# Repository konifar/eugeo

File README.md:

# eugeo

6 キー × 4 行 × 2 ブロック（48 キー）のスルーホール・オーソリニア 40% キーボード PCB です。
[Lumberjack](https://github.com/peej/lumberjack-keyboard)（Paul James 作、MIT License）をベースに、行を 1 段減らし、Kailh の MX 用ホットスワップソケットに対応させました。

| 真上 | 背面 | 側面（6°） |
|---|---|---|
|  |  |  |

組み上がりの画像のスイッチとキーキャップは、大きさと位置の目安として置いた簡易形状です（`scripts/preview_models.py`）。

## Lumberjack からの変更点

| | Lumberjack Rev 1.8 | eugeo Rev 1.0 |
|---|---|---|
| 配列 | 5 × 12（60 キー） | 4 × 12（6 × 4 × 2、48 キー） |
| スイッチ | はんだ付け | Kailh MX ホットスワップソケット（裏面） |
| マトリクス | 6 行 × 10 列 | 8 行 × 6 列（後述） |
| USB-C | 左上・裏面 | 中央上・裏面（ソケットとの干渉回避） |
| 外形 | 60% トレイマウントケース互換 | 284.9 × 75.35 mm。プレートと基板を M2 穴 8 箇所でサンドイッチし、プレートのタブでガスケットマウント |
| ドーターボード用コネクタ (J3-J5) | あり | 削除 |
| 中央カバー | 2 mm アクリル、M2 10 mm スペーサー 4 本 | 同じ構成（ネジはカバーの四隅） |
| マイコン | ATmega328P-PU（DIP）+ V-USB（USB 1.1 Low Speed） | RP2040 + 2 MB QSPI フラッシュ（USB Full Speed、UF2 書き込み） |
| 電源 | USB 5 V 直結 | MCP1700 で 3.3 V（TO-92） |
| 書き込み | ISP ヘッダ（2x3） | BOOT ボタン + USB（UF2）。ISP ヘッダは不要になったので削除 |

マイコンまわりの表面実装部品（RP2040、フラッシュ、0402 のコンデンサなど）は JLCPCB に実装してもらい、それ以外はスルーホール部品のまま残しています。
上部の左右に 1 個ずつの LED、水晶（HC49）、セラミック・電解コンデンサ、LDO（TO-92）、アキシャル抵抗、タクトスイッチ、ダイオード列が中央に並ぶ、Lumberjack の「部品を見せる」見た目を踏襲しています。

## マトリクス

左右のブロックで行を分け、列を共有させた 8 行 × 6 列です。
左右の対称位置の列（左 C0 と右 C11 など）を基板下端の 1 本の配線で共有するので、ROW の配線が MCU をまたがずに済みます。
RP2040 の左辺のピンから左ブロックの行・列 3 本・LED1、右辺のピンから右ブロックの行・列 3 本・LED2 を出し、下辺は水晶と RUN、上辺は QSPI フラッシュと USB に使っています。

| 物理位置 | マトリクス |
|---|---|
| 左ブロック (row r, col c) | ROW r, COL c |
| 右ブロック (row r, col 6+j) | ROW r+4, COL 5-j |

| 設定 | 値 |
|---|---|
| MATRIX_ROW_PINS | GP3, GP4, GP5, GP6, GP26, GP25, GP24, GP23 |
| MATRIX_COL_PINS | GP9, GP10, GP11, GP20, GP19, GP18 |
| DIODE_DIRECTION | COL2ROW |
| LED1 (赤) / LED2 (緑) | GP1 / GP28（上部の左右） |
| BOOT ボタン | QSPI_SS（RP2040 標準の BOOTSEL。1k 経由で GND に落とす） |

## ファイル構成

| パス | 内容 |
|---|---|
| `eugeo.kicad_pro` / `.kicad_sch` / `.kicad_pcb` | KiCad 9 プロジェクト |
| `symbols/`, `footprints/eugeo.pretty/` | プロジェクト専用シンボル・フットプリント（ホットスワップソケット、USB-C、M2 穴） |
| `plates/` | スイッチプレート（ガスケット用タブ付き、左右共通で 2 枚注文）、中央カバー、ボトムプレートの KiCad データと DXF |
| `case/` | Mojo60 風の丸いガスケットマウントケース（下トレイ `eugeo-case-bottom` + 上フレーム `eugeo-case-top`）と中央カバーの STEP / STL |
| `foam/` | プレートフォーム・ケースフォーム・ガスケットパッドの DXF と原寸 PDF |
| `lasercut/yushakobo/` | 遊舎工房レーザー加工サービス用の SVG（中央カバー / スイッチプレート / フォーム） |
| `jlcpcb/` | JLCPCB 実装用 BOM / CPL（表面実装部品とホットスワップソケット） |
| `jlcpcb/full/` | USB-C とスルーホール部品まで JLCPCB に実装してもらう場合の BOM / CPL |
| `gerbers/*.zip` | 製造用ガーバー（PCB、プレート、ボトム） |
| `firmware/qmk/keyboards/eugeo/` | QMK 用キーボード定義とキーマップ（default / via） |
| `firmware/*.uf2` | ビルド済みファームウェア |
| `scripts/` | 回路図・基板・裏面アート（`stump_art.py`）を生成するスクリプト一式 |

## 生成手順

回路図と基板は `scripts/design.py` を唯一の定義として生成しています。
部品配置やネットを変えるときは `design.py` を編集して再生成してください。

```bash
FREEROUTING_JAR=/path/to/freerouting-2.1.0.jar scripts/build_all.sh
```

1. `gen_schematic.py` で回路図を生成し、`check_netlist.py` で `design.py` とネットを照合
2. `build_pcb.py` で部品配置と、キー部分・ダイオード列・USB 端子・RP2040 まわりの配線を引く。RP2040 は電源ピンをパッドの内側の +3V3 リングでまとめ、QSPI・水晶・パスコン・各ピンの引き出しまでを手配線している
3. `route.sh` で残り（引き出した先から各部品まで）を Freerouting 2.1.0 で自動配線
4. `cleanup_dangling.py` で余った配線を削除し、`fill_zones.py` で表裏の GND ベタを流し、`stump_art.py` で裏面のアートを描く
5. DRC（回路図との整合チェック込み）

Freerouting の結果は実行ごとに変わり、まれに未配線が残ります。その場合は `build_all.sh` を再実行してください。
Freerouting 2.1.0 は Java 21 で動きます（2.2 以降は Java 25 が必要）。
初回起動時にできる設定ファイル（macOS では `$TMPDIR/freerouting/freerouting.json`）はテレメトリが有効なので、`allow_telemetry` を `false` にしておくことを勧めます。

製造データは次のコマンドで出力します。

```bash
scripts/export_fab.sh
```

## 製造（JLCPCB）

2026-10-06 に JLCPCB / JLC3DP の見積もりページへアップロードし、次のとおり受け付けられることを確認しました（カート投入・注文はしていません）。

| 部品 | ファイル | JLCPCB の認識 | 見積もり（参考） |
|---|---|---|---|
| PCB | `gerbers/eugeo.zip` | 2 層、284.9 × 75.35 mm | 5 枚 ¥2,269 + 送料 ¥1,536 |
| スイッチプレート | `gerbers/eugeo-plate.zip` | 2 層、113.45 × 75.35 mm。外形レイヤーにスイッチ穴 24 個と M2 穴 4 個（ガスケット用タブを付ける前の版。今の版はタブ込みで 118.45 × 85.35 mm） | 5 枚 ¥630 |
| ケース | `case/eugeo-case.step` | 302.9 × 93.4 × 29.9 mm、198.09 cm³（ふちを上げる前・一体型の版） | 9600 Resin 白 1 個 ¥2,978 + 送料 ¥1,139。MJF ナイロン（PA12）なら グレー ¥11,651、黒染め ¥12,945（2026-10-17） |

PCB の注文設定は既定値（FR-4、1.6 mm、HASL）のままで問題ありません。色は好みで変えてください。
スイッチプレートは銅箔のない基板として注文します。JLCPCB の 2D プレビューでは穴が描かれませんが、Gerber Viewer の Layers 表示で外形に穴が入っていることを確認できます。左右共通なので 2 枚以上あれば足ります。
ボトムプレート（`gerbers/eugeo-bottom.zip`）はケースを使わない場合だけ必要です。

ケースは JLC3DP の 3D Printing で `case/eugeo-case-bottom.step` と `case/eugeo-case-top.step`（または `.stl`）の 2 つをアップロードし、素材に MJF ナイロン（PA12）を選びます。
MJF の最大造形サイズ（380 × 284 × 380 mm）に収まります。
すき間は MJF の寸法公差（±0.3 mm、100 mm を超える部分は ±0.3 %、長さ 303 mm で片側約 0.45 mm）と、内外を塗装したときの塗膜（1 面 0.1〜0.2 mm）を見込んで決めています（ネジ穴 φ2.8、ネジ頭の座ぐり φ5.0、ナット穴 二面幅 4.7 mm）。SLA レジンでも同じデータで作れます。
2026-11-14 は SLA の 9600 Resin 白（Sanding-General Sanding）で注文し、塗装は自分でする（上下で ¥3,265、製作 3 日。MJF PA12 は無塗装で ¥11,905、黒マット塗装付きで ¥13,867）。自分で塗るときは、ネジ穴とナット穴をマスキングしてから黒のサーフェイサー → つや消し黒 → UV カットのつや消しクリアの順に吹く。

### 表面実装部品とソケットの実装を JLCPCB に頼む

RP2040 まわりの表面実装部品（表面）とホットスワップソケット 48 個（裏面）を JLCPCB の PCBA で実装し、残りのスルーホール部品は自分ではんだ付けする想定です。
表裏両面の実装になるので Standard PCBA を選び、Assembly Side は **Both Sides** にして次のファイルをアップロードします。

| ファイル | 内容 |
|---|---|
| `jlcpcb/eugeo-bom.csv` | ソケット（LCSC C41430893）と表面実装部品（RP2040 C2040、W25Q16JVSSIQ C131025、USBLC6-2SC6 C7519、0402 のコンデンサ・抵抗。R7 / R8 / C12 / C13 / U4 は裏面） |
| `jlcpcb/eugeo-cpl.csv` | 実装座標（ガーバーと同じ原点）。ソケットは本体中心・裏面・回転 0、表面実装部品は KiCad の部品位置 |

2026-10-08 に実際にアップロードして確認した結果です（カート投入・注文はしていません）。

- ガーバー: 2 層、284.9 × 75.35 mm として受け付け。Standard PCBA では JLCPCB が上下に 5 mm の捨て基板（エッジレール）を付けるので、届いた基板はレールを折って外す（有料の Depanel オプションで外してもらうこともできる）
- BOM: 7 品目すべてが LCSC 部品に一致（RP2040 C2040、W25Q16JVSSIQ C131025、USBLC6-2SC6 C7519、0402 のコンデンサ・抵抗、ソケット C41430893）
- 部品配置プレビューで、RP2040・フラッシュ・USBLC6 の 1 番ピンとリードがフットプリントに合うことを確認。KiCad の角度のままではフラッシュ（SOIC-8、表）と USBLC6（SOT-23-6、裏）が 90° ずれていたので、`scripts/export_jlc_pcba.py` の `ROT_OFFSET` で補正済み。USBLC6 は 180° 間違えると GND と VBUS が入れ替わるので、部品を変えたときは必ずプレビューで確かめる
- ソケットの回転は 2026-10-06 に確認済み（突起が φ3.05 穴に、端子がパッドに重なる）
- 見積もり: 5 枚で ¥18,706（PCB ¥2,490、PCBA ¥16,215。うち初期費用 ¥8,117、ステンシル ¥2,607、部品 ¥3,406）、送料別

Kailh 純正ソケット（C5184526）にしたい場合は `scripts/export_jlc_pcba.py` の `LCSC` を書き換えてください。

### すべての部品の実装を JLCPCB に頼む

USB-C とスルーホール部品（ダイオード 48 本、抵抗、コンデンサ、水晶、レギュレータ、タクトスイッチ、LED）まで JLCPCB に付けてもらう場合は、`jlcpcb/` の代わりに `jlcpcb/full/` をアップロードします（`python3 scripts/export_jlc_pcba.py --full` で生成）。はんだ付けは不要になり、届いたらスイッチを挿すだけです。

2026-10-08 にアップロードして確認した結果です（カート投入・注文はしていません）。

- BOM: 22 品目すべてが LCSC 部品に一致し、在庫あり
- スルーホール部品の座標は KiCad の原点（1 番ピン）ではなくパッドの中心にしている。USB-C は SMD なので部品位置のまま
- 部品配置プレビューで向きを確認。JLCPCB のモデルでは 3 mm LED のカソードと USB-C の差し込み口が逆向きだったので、`ROT_OFFSET` で 180° 補正済み
- 見積もり: 5 枚で ¥27,679（PCB ¥2,490、PCBA ¥25,188。うち初期費用 ¥8,117、ステンシル ¥2,607、部品 ¥6,949、フィーダー ¥1,954、手はんだ ¥569、手作業実装 ¥1,989、治具 ¥2,607）、送料別。表面実装部品とソケットだけの場合より ¥8,973 高い
- コンデンサ C6 / C7（C1620326）は単価が高く在庫も少なめ（確認時 34 個）、レギュレータ U3（C511277）も在庫 349 個。注文時に在庫切れなら同等品に差し替える

## 裏面のデザイン

基板の裏面は「凍てついた切り株」がテーマです（`scripts/stump_art.py`、`build_all.sh` の中で自動生成）。

- 裏返して左側（表から見て右ブロックの 1 段目と 2 段目の間）に、ケース背面の刻印と同じ Futura の「EUGEO」ロゴを大きく入れている。文字の高さ 7.5 mm、両側に細い線と丸を添える。文字の輪郭は `scripts/logo_outline.py` で `scripts/logo_eugeo.json` に書き出したもの

- 中央に年輪・樹皮・干割れのある切り株をシルクで描き、左右の端に向かって霜の結晶（シダ状の霜）が伸びる
- キーの並ぶ部分にはシルクの雪の結晶を散らす
- 大きめの雪の結晶 7 個はソルダーレジストの開口で、GND ベタの銅がそのまま（HASL なら銀色に）見える。配線・ビア・穴のない GND ベタの上にだけ置く
- シルクはパッド・穴・既存の文字の周りで自動的に切り取り、DRC の警告が出ないようにしている

レジストの色は青（Blue）を勧めます。白いシルクと銀色の結晶が氷のように見えます。

## ケース

Mojo60 を意識した、角と上下のふちを大きく丸めたガスケットマウントのケースです。プレートの中ほどの高さで、下トレイと上フレームの 2 つに分かれています。

| 項目 | 値 |
|---|---|
| 外形 | 302.9 × 93.4 mm、高さ 手前 23.1 mm / 奥 32.9 mm |
| 傾斜 | 6° |
| 角の丸み | 平面 R12、上面のふち R6.5、底面のふち R4.5 |
| ふち | プレート上面から 6.5 mm 上（スイッチの上部が隠れ、キーキャップはその上に出る高さ） |
| 基板と壁のすき間 | 1.0 mm（キーキャップと壁の間は約 1.1 mm） |
| 底面 | 肉抜きして、幅 7 mm のふちで接地。肉抜きには厚さ 2 mm の格子リブ（前後 7 本、左右 1 本）を入れ、床の鳴りと反りを抑える。ネジ穴のまわりは肉を 1.5 mm 以上残す |
| 分割 | プレートの厚さの中央（基板上面から 4.25 mm）で上下に分割。下トレイ 25.2 mm、上フレーム 7.3 mm |
| 刻印 | 奥の壁に「EUGEO」の銘板（後述） |

### 刻印

奥の壁の USB-C の横（背面から見て右）に、銘板風の刻印を入れています。
USB-C の切り欠きと同じ高さ 8.5 mm の長円を 0.6 mm 掘り下げ、Futura の「EUGEO」（文字高さ約 4.4 mm、字間広め）と両端の小さな鋲を元の壁面の高さで残しています。
USB-C の切り欠きと形・高さを揃えて、背面の 2 つの要素が並んで見えるようにしました。

文字・フォント・位置・深さは `scripts/case.py` の `BADGE_*` 定数で変えられます。

寸法は `scripts/case.py` の先頭にある定数で変えられます。再生成の手順は次のとおりです。

```bash
uv venv --python 3.12 .venv && uv pip install --python .venv/bin/python build123d
.venv/bin/python scripts/case.py
kicad-cli pcb export step --subst-models -o /tmp/eugeo-pcb.step eugeo.kicad_pcb
.venv/bin/python scripts/check_case_fit.py /tmp/eugeo-pcb.step   # 基板・部品・プレートとの干渉チェック
```

### ガスケットマウント

左右のスイッチプレートの外周にタブ（幅 10 mm、外へ 5 mm）が 5 本ずつあり、ケースの壁の溝の中で上下から PORON のパッドに挟まれています。
基板はスペーサーでプレートにぶら下がっていて、ケースのどこにも触れません。打鍵の力はパッドで受けるので、たわみと音がやわらかくなります。

| 項目 | 値 |
|---|---|
| タブ | 1 枚のプレートに奥 2 本・手前 2 本・外側 1 本（左右で計 10 本）。左右共通の形で、右側は裏返して使う |
| パッド | 3 mm PORON を 10 × 4 mm に切ったもの 20 個（タブの上下に 1 個ずつ）。溝の中では 2.2 mm に縮む（約 27%） |
| 溝 | タブより左右に 0.5 mm、先端に 1 mm 大きい。高さはプレート 1.5 mm + パッド 2.2 mm × 2 |
| 基板のすき間 | 壁とは 1 mm。ケースの底とは、キー部分が 2.8 mm（3 mm のケースフォームを 0.2 mm つぶして基板の裏に当てる）、中央の部品エリアが 5 mm |
| 上下の固定 | M2×10 なべネジ 8 本を底から通し、上フレームに埋めた M2 ナットで締める |

`scripts/check_case_fit.py` で、基板・部品・プレート・タブがケースに当たらないことと、10 本のタブすべてで上下のパッドの厚みが確保されていることを確かめています。

### 組み立て

インサートを使わずに済むよう、上下のケースは底からネジで留めます。

1. 基板の上面の M2 穴 8 か所（H1〜H8）に M2 3.5 mm のメス-メススペーサーを立て、基板の裏から M2×3 で留める
2. スイッチをプレートにはめ、基板のソケットに差し込み、プレートの上から M2×3 でスペーサーに留める（右のプレートは左と同じものを裏返して使う）
3. 中央カバーを付ける（後述）
4. 上フレームのナット穴（下面）に M2 ナットを 8 個入れる。抜けやすい場合はマスキングテープか少量の接着剤で仮止めする
5. 下トレイの溝の底と、上フレームの溝の天井にガスケットパッドを貼る（PORON は粘着なしなので、両面テープで軽く留める）
6. ケースフォームを下トレイの一段高い床に置き（左右で形が違うので `L` / `R` を確かめ、裏返さない）、基板とプレートの組を載せてタブを溝に合わせる
7. 上フレームをかぶせ、底から M2×10 を 8 本締める。締めすぎるとパッドがつぶれてガスケットの効果がなくなるので、上下が接したところで止める

奥の壁の USB-C 用の切り欠きは 14 × 9.5 mm です（基板がパッドの上で動くぶん、一体型のときより 1 mm 高くしています）。プラグのモールド部分がこれより大きいケーブルは奥まで刺さりません。
底面の四隅に平らな面を残してあるので、直径 8〜10 mm のゴム足を 4 個貼ってください（中心はケースの左右の端から約 10 mm、前後の端から約 10 mm）。

## 中央カバー

Lumberjack と同じく、中央の部品（ダイオード列・MCU・USB 周り）を透明な板で覆えます。

| 項目 | 値 |
|---|---|
| 大きさ | 56.2 × 75.35 mm、角 R3、厚さ 2 mm |
| 取り付け | カバーの四隅に合わせた基板の M2 穴 4 か所（H9〜H12）に M2 10 mm のメス-メススペーサーを立て、下から M2×4 で基板に、上から M2×4 でカバーを留める |
| 高さ | カバーの下面は基板上面から 10 mm。下でいちばん高い LED1（8.29 mm）との間に 1.71 mm のすき間 |
| ケースとの関係 | カバーの上面はケースのふちより約 0.5 mm 上。ケース・キーキャップとは重ならない |

| ファイル | 用途 |
|---|---|
| `plates/eugeo-cover.dxf` | アクリル板のレーザーカット用（推奨） |
| `case/eugeo-cover.step` / `.stl` | 3D プリントや CNC 用 |
| `gerbers/eugeo-cover.zip` | JLCPCB で FR4 板として作る場合（不透明になる） |

JLCPCB の基板サービスでは透明な板は作れないため、透明にしたい場合はアクリルのレーザーカットサービスに DXF を出してください。
JLC3DP の SLA で作る場合は、見積もり画面で透明系のレジンが選べるか確認してください。

## フォーム

打鍵音とたわみの調整用の 2 種類のフォームと、ガスケットマウント用のパッドの型を用意しました。プレートフォームは左右同じ形なので 1 つの型で 2 枚切り、片方は裏返して使います。ケースフォームはソケットの向きが左右で同じため、左用と右用で形が違います（裏返さずにそのまま置く）。

| ファイル | 位置 | 推奨素材 | 形 |
|---|---|---|---|
| `foam/eugeo-plate-foam` | プレートと PCB の間（3.5 mm） | 3 mm PORON | プレートと同じ外形、スイッチ下部を逃がす 14.5 mm 角穴、スペーサー用 φ4.4 穴 |
| `foam/eugeo-case-foam-left` / `-right` | PCB とケース底の間（キー部分 2.8 mm） | 3 mm PORON | キー部分のみ（中央の部品エリアは空ける）。ホットスワップソケット・はんだ付けの足・スイッチの中心軸と足を 0.5 mm 大きく逃がす穴と、基板の裏のネジ頭を逃がす φ7 穴。外形との間が 2 mm 未満になるところは切り欠きにしている |
| `foam/eugeo-gasket-pad` | プレートのタブの上下（ケースの溝） | 3 mm PORON | 10 × 4 mm、20 個 |

`.dxf` はレーザーカット業者向け、`-1to1.pdf` は手で切るための原寸の型紙です。PDF は A4 横で、倍率 100% で印刷し、100 mm のスケールバーで寸法を確かめてから使ってください。
ケースのキー部分の床は基板の裏から 2.8 mm の高さに上げてあり、3 mm のケースフォームがソケットを避けながら基板の裏に軽く当たります。ソケットやスイッチの足にフォームが当たらないことは `scripts/check_case_fit.py` で確かめています。
JLCPCB ではフォームのカットは扱っていないため、遊舎工房のレーザー加工（下記）に出すか手で切ってください。
スイッチプレートは、ケースの内側に 1 mm のすき間で収まり、ケースのふちより 6.5 mm 低い位置に来ることを確認済みです。

## 遊舎工房のレーザー加工

[遊舎工房のレーザー加工サービス](https://yushakobo.jp/lasercut/)に、そのまま入稿できる SVG を `lasercut/yushakobo/` に用意しました。
遊舎工房配布の Inkscape テンプレートを土台にし、注文サイズの作業領域だけを残しています。

| ファイル | 注文するサービス / 素材 / 厚さ / サイズ | 中身 |
|---|---|---|
| `eugeo-cover_acrylic-clear-2mm_450x300.svg` | [レーザー加工サービス](https://shop.yushakobo.jp/products/lasercut)（アクリル）/ アクリル クリア / 2mm / 450x300 | 中央カバー 26 枚（縦向き 7 枚 × 3 段 + 横向き 5 枚） |
| `eugeo-switch-plate_pom-1.5mm_490x245.svg` | [レーザー加工サービス（その2）](https://shop.yushakobo.jp/products/lasercut-2) / POM / 1.5mm / 490x245 | ガスケット用タブ付きスイッチプレート 8 枚（4 台分。左右共通、右は裏返して使う）。隣り合うプレートのタブを互い違いにかみ合わせ、4 mm 空けて並べている |
| `eugeo-foam_poron-3mm_500x300.svg` | レーザー加工サービス（その2）/ フォーム / 3mm / 500x300 | キーボード 3 台分。プレートフォーム 6 枚 + ケースフォーム左右 3 組 + ガスケットパッド 60 個（1 段目〜3 段目が 1 台分ずつ） |

- 穴などの内側はカット①（赤）、外形はカット②（青）です。内側を先に切ってから部品を切り離す順番になります
- 線幅 0.001 mm、塗りなし、RGB、ファイル名は半角英数字です。シート端から 3.5 mm 以上、部品同士は 3 mm 以上空けています（規定は 3 mm / 2 mm 以上。部品同士はタブ込みの外形どうしの距離で `check_lasercut_svg.py` が確かめる）
- レーザーは線の上を切るため、穴は線より少し大きく、外形は少し小さく仕上がります。POM プレートのスイッチ穴（14.0 mm）が緩い場合は、注文時に相談してください
- スイッチプレートは JLCPCB の FR4（`gerbers/eugeo-plate.zip`、1.6 mm）と POM のどちらで作っても同じ形です。ガスケットマウントでは、たわむ POM のほうが向いています

テンプレートはリポジトリに含めていません。作り直すときは、遊舎工房の [Laser_Cut_template](https://drive.google.com/drive/folders/1BYeC-_gsrWUxI49BNqbQBk6OOC30LgTS) の Inkscape フォルダにある `Laser_acrylic_template.svg`、`Laser_POM_template.svg`、`Laser_Poron_template.svg` を 1 つのフォルダに置き（POM / Poron はファイル名を小文字の `pom` / `poron` にする）、次を実行します。

```bash
python3 scripts/export_yushakobo_svg.py <テンプレートのフォルダ>
python3 scripts/check_lasercut_svg.py
```

## 組み立て（基板）

- ホットスワップソケットと USB-C は裏面、それ以外の部品は表面に付けます
- ダイオードは帯（カソード）を MCU 側に向けます。左列はシルクの右側、右列は左側がカソードです
- プレートと PCB の間は 3.5 mm（1.5 mm 厚プレートでスイッチ底面が PCB に接する高さ）です
- ケースを使わずボトムプレートで挟む場合は、裏面の USB-C とソケットを避けるため PCB とボトムの間を 8 mm 程度空けます

## ファームウェア

`firmware/qmk/keyboards/eugeo` を qmk_firmware の `keyboards/` にコピーしてビルドします。
2026-10-07 時点の qmk_firmware でビルドできることを確認済みです。ビルド済みの `firmware/eugeo_default.uf2` / `firmware/eugeo_via.uf2` も置いてあります。

```bash
qmk compile -kb eugeo -km via
```

RP2040 は ROM にブートローダーを持っているので、ブートローダーの書き込みは要りません。

1. BOOT を押したまま RESET を押して離す（何も書き込まれていない新品の RP2040 は USB をつなぐだけでよい）
2. `RPI-RP2` という USB ドライブとして認識される
3. `eugeo_via.uf2` をそのドライブにコピーすると、書き込み後に自動で再起動する

`qmk flash -kb eugeo -km via` でも同じことができます。キーマップに `QK_BOOT` を割り当てておけば、BOOT ボタンを使わずに書き込みモードに入れます。

### Remap / VIA

`via` キーマップは VIA 対応（`VIA_ENABLE = yes`）で、[Remap](https://remap-keys.app) と VIA のどちらからでもキー配置を変えられます。

1. Chrome か Edge で Remap を開き、「Configure」から eugeo を接続する
2. Remap のカタログに未登録のうちは定義ファイルを求められるので、`firmware/via/eugeo.json` を読み込む

`firmware/via/eugeo.json` は VIA v3 形式の定義ファイルで、物理配列どおり左右ブロックの間を 3U 空けています。VIA の Design タブでもそのまま読み込めます。
Remap のカタログに登録すると、Remap の画面からファームウェアの書き込み（UF2 のダウンロードとコピーの案内）もできるようになります。

Remap のカタログに登録すれば、定義ファイルを読み込まなくても自動で認識されます。登録は Remap に GitHub アカウントでログインして申請し、ファームウェアのソースの場所（GitHub のリポジトリなど）を示します。
VID / PID（`0x6B6E` / `0x4547`）は自分で決めた値です。登録前に、他のキーボードと重複していないか Remap 上で確認してください。

## 動作の検証

実機は作っていないため、基板データからの検証で、はんだ付けすれば動くことを確認しています。

- KiCad の DRC: 違反 0、未接続 0、回路図との整合 OK。ERC も 0 件
- `scripts/verify_design.py`（59 項目すべて合格）
  - RP2040 のシンボルのピン名がデータシート（QFN-56）と一致すること
  - 電源: IOVDD 6 本・ADC_AVDD・VREG_VIN・USB_VDD が +3V3、VREG_VOUT が DVDD 2 本に、パスコンの数と RP2040 からの距離、MCP1700 のピン配置
  - 12 MHz 水晶と 1k 直列抵抗、22 pF、RUN のプルアップと RESET、BOOT（QSPI_SS を 1k で GND へ）
  - QSPI フラッシュの 8 ピンが RP2040 の QSPI 信号と一致すること
  - USB: D+ / D- が 27Ω 経由で USB_DP / USB_DM に、USBLC6、CC の 5.1k、VBUS のポリスイッチ
  - LED とコンデンサの極性、ダイオードの向き（COL2ROW）、QMK の LED ピン設定
  - 48 キーすべてについて、基板上の行・列の GPIO が QMK の `keyboard.json` と一致すること
- RP2040 まわりは、電源ピンをパッドの内側の +3V3 リングでまとめ、+1V1 は裏面経由で 3 ピンをつなぎ、QSPI・水晶・パスコン・行と列の引き出しまでを手配線しています。0.4 mm ピッチの間をすり抜ける配線はありません
- 中央カバー: カバー下面と部品の最小すき間 1.71 mm（LED1）、カバーとケース・部品の干渉 0（`scripts/check_case_fit.py`）
- ソケットのフットプリント: パッド位置・サイズが [keyswitch-kicad-library](https://github.com/perigoso/keyswitch-kicad-library) の SW_Hotswap_Kailh_MX_1.00u と一致。ソケットの突起が入る穴は同ライブラリに合わせて φ3.05 mm

```bash
KP=/Applications/KiCad/KiCad.app/Contents/Frameworks/Python.framework/Versions/Current/bin/python3
$KP scripts/verify_design.py
```

### 発注前チェック

発注の前に `scripts/preorder_check.py` を実行してください（2026-10-07 時点で 23 項目すべて合格）。DRC で見えない次の点を確かめます。

- 前の版との差分が、意図した部品の追加・削除だけであること（ほかのパッドの位置と接続が変わっていない）
- 全部品が `design.py` どおりの位置・向き・面にあり、外形も設計どおりであること
- スペーサー・ネジ頭が当たる範囲に、むき出しの銅箔がないこと。ビアがすべてレジストで覆われていること（マスクのガーバーでも確認）
- 実際の基板の最小値（線幅 0.15、ビア φ0.3 / 0.6、穴、スロット、シルク文字 1.0 mm）が JLCPCB の製造基準を満たすこと
- `gerbers/eugeo.zip` が今の基板から出したものと一致し、ドリルデータに M2 穴 12 個が設計位置どおりにあること
- JLCPCB の実装座標（ソケットと表面実装部品）と LCSC 番号、スイッチプレート・中央カバー・ボトムプレートの穴が基板の穴と一致すること
- 遊舎工房向け SVG が入稿ルールを満たすこと、59 項目の機能チェックが通ること

```bash
$KP scripts/preorder_check.py --base <前回発注した版の git リビジョン>
```

## 未検証の点

- 試作していません。上記の検証、ケースとの干渉チェックは通っています
- JLCPCB の部品の回転角はプレビューで確認しただけです。部品を変えたら注文時の配置プレビューで 1 番ピンの向きを確かめてください（上の「表面実装部品とソケットの実装を JLCPCB に頼む」）
- USB-C コネクタ（TYPE-C-31-M-12）は 0.5 mm ピッチの SMD で、手はんだでは一番難しい部品です（Lumberjack と同じ部品）
- ケースの USB-C 部はコネクタの 3D モデルがないため、寸法計算だけで確認しています
- ホットスワップソケットのフットプリントは keyswitch-kicad-library と同寸で、JLCPCB の部品配置とも一致しましたが、実物のソケットでの勘合は未確認です

## License

ハードウェア（回路図・基板・プレート・ケース・フォーム）とスクリプトは MIT License です。Lumberjack の著作権表示を `LICENSE` に残しています。
`firmware/qmk/` 以下のファームウェアは QMK に合わせて GPL-2.0-or-later です。

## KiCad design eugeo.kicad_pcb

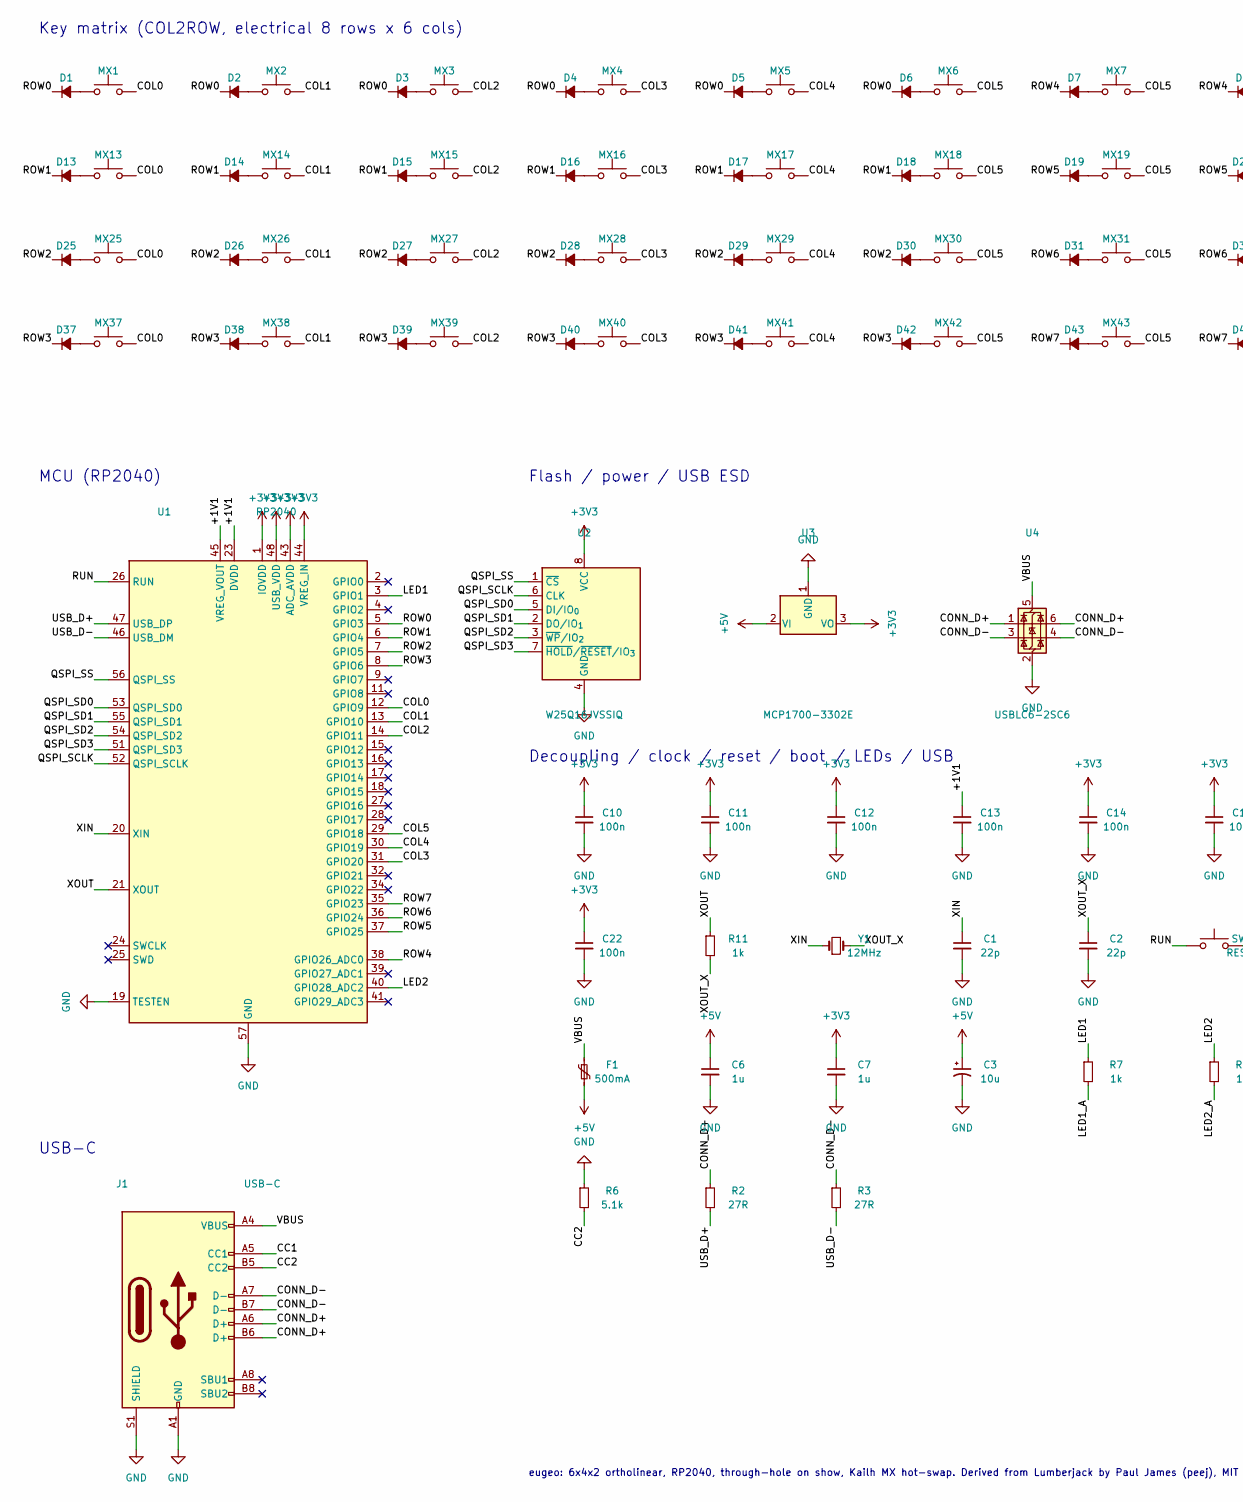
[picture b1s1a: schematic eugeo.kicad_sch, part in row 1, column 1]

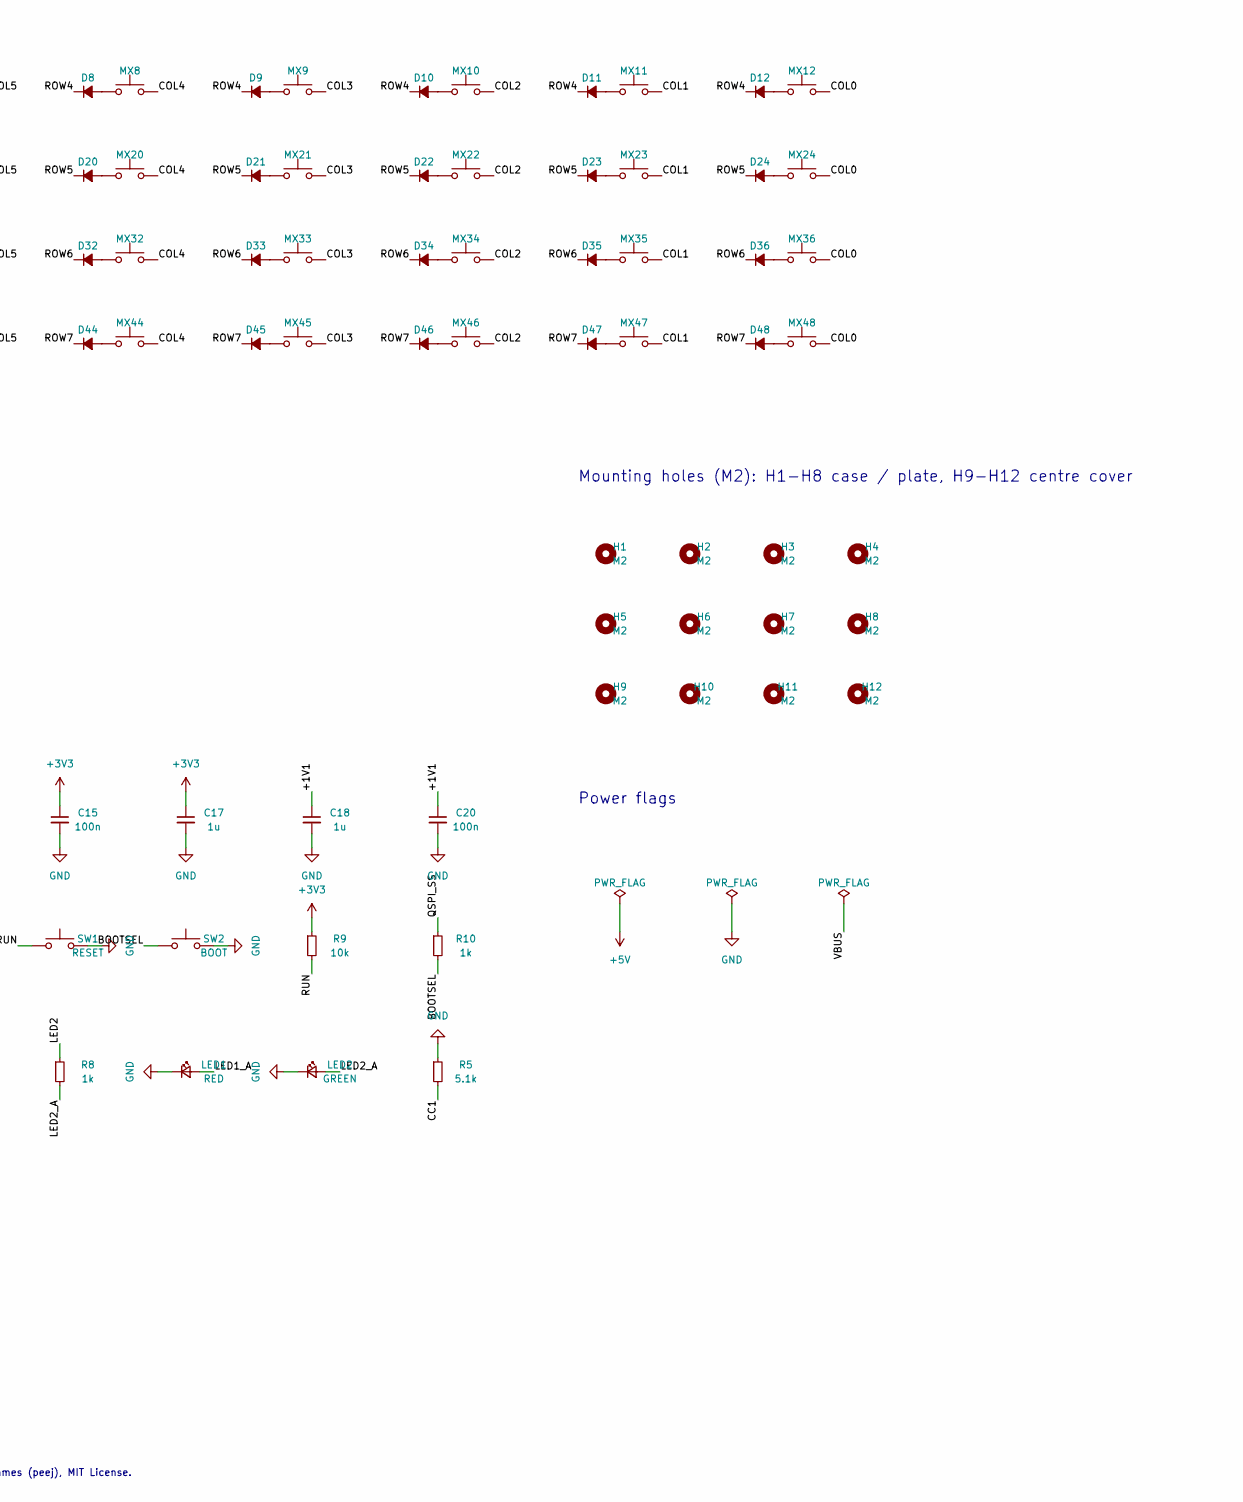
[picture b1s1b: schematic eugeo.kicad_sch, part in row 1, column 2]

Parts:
C1, C2: 22p; C_Disc_D3.0mm_W1.6mm_P2.50mm
C3: 10u; CP_Radial_D4.0mm_P1.50mm
C6, C7: 1u; C_Disc_D3.0mm_W2.0mm_P2.50mm
C10, C11, C12, C13, C14, C15, C20, C22: 100n; C_0402_1005Metric
C17, C18: 1u; C_0402_1005Metric
D1, D2, D3, D4, D5, D6, D7, D8, D9, D10, D11, D12, D13, D14, D15, D16, D17, D18, D19, D20, D21, D22, D23, D24, D25, D26, D27, D28, D29, D30, D31, D32, D33, D34, D35, D36, D37, D38, D39, D40, D41, D42, D43, D44, D45, D46, D47, D48: 1N4148; D_DO-35_SOD27_P7.62mm_Horizontal
F1: 500mA; Fuse_1206_3216Metric
H1, H2, H3, H4, H5, H6, H7, H8, H9, H10, H11, H12: M2; MountingHole_M2_NPTH
J1: USB-C; TYPE-C-31-M-12
LED1: RED; LED_D3.0mm
LED2: GREEN; LED_D3.0mm
MX1, MX2, MX3, MX4, MX5, MX6, MX7, MX8, MX9, MX10, MX11, MX12, MX13, MX14, MX15, MX16, MX17, MX18, MX19, MX20, MX21, MX22, MX23, MX24, MX25, MX26, MX27, MX28, MX29, MX30, MX31, MX32, MX33, MX34, MX35, MX36, MX37, MX38, MX39, MX40, MX41, MX42, MX43, MX44, MX45, MX46, MX47, MX48: MX; MX_Hotswap_Kailh
R2, R3: 27R; R_Axial_DIN0204_L3.6mm_D1.6mm_P7.62mm_Horizontal
R5, R6: 5.1k; R_Axial_DIN0204_L3.6mm_D1.6mm_P7.62mm_Horizontal
R7, R8, R11: 1k; R_0402_1005Metric
R9: 10k; R_Axial_DIN0204_L3.6mm_D1.6mm_P7.62mm_Horizontal
R10: 1k; R_Axial_DIN0204_L3.6mm_D1.6mm_P7.62mm_Horizontal
SW1: RESET; SW_PUSH_6mm
SW2: BOOT; SW_PUSH_6mm
U1: RP2040; QFN-56-1EP_7x7mm_P0.4mm_EP3.2x3.2mm
U2: W25Q16JVSSIQ; SOIC-8_5.3x5.3mm_P1.27mm
U3: MCP1700-3302E; TO-92_Inline_Wide
U4: USBLC6-2SC6; SOT-23-6
Y1: 12MHz; Crystal_HC49-4H_Vertical

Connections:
+3V3: C7.1, C10.1, C11.1, C12.1, C14.1, C15.1, C17.1, C22.1, R9.1, U1.1 (IOVDD), U1.10 (IOVDD), U1.22 (IOVDD), U1.33 (IOVDD), U1.42 (IOVDD), U1.43 (ADC_AVDD), U1.44 (VREG_IN), U1.48 (USB_VDD), U1.49 (IOVDD), U2.8 (VCC), U3.3 (VO)
+5V: C3.1, C6.1, F1.2, U3.2 (VI)
/+1V1: C13.1, C18.1, C20.1, U1.23 (DVDD), U1.45 (VREG_VOUT), U1.50 (DVDD)
/BOOTSEL: R10.2, SW2.1
/CC1: J1.A5 (CC1), R5.2
/CC2: J1.B5 (CC2), R6.2
/COL0: MX1.2, MX12.2, MX13.2, MX24.2, MX25.2, MX36.2, MX37.2, MX48.2, U1.12 (GPIO9)
/COL1: MX2.2, MX11.2, MX14.2, MX23.2, MX26.2, MX35.2, MX38.2, MX47.2, U1.13 (GPIO10)
/COL2: MX3.2, MX10.2, MX15.2, MX22.2, MX27.2, MX34.2, MX39.2, MX46.2, U1.14 (GPIO11)
/COL3: MX4.2, MX9.2, MX16.2, MX21.2, MX28.2, MX33.2, MX40.2, MX45.2, U1.31 (GPIO20)
/COL4: MX5.2, MX8.2, MX17.2, MX20.2, MX29.2, MX32.2, MX41.2, MX44.2, U1.30 (GPIO19)
/COL5: MX6.2, MX7.2, MX18.2, MX19.2, MX30.2, MX31.2, MX42.2, MX43.2, U1.29 (GPIO18)
/CONN_D+: J1.A6 (D+), J1.B6 (D+), R2.1, U4.1 (I/O1), U4.6 (I/O1)
/CONN_D-: J1.A7 (D-), J1.B7 (D-), R3.1, U4.3 (I/O2), U4.4 (I/O2)
/LED1: R7.1, U1.3 (GPIO1)
/LED1_A: LED1.2 (A), R7.2
/LED2: R8.1, U1.40 (GPIO28_ADC2)
/LED2_A: LED2.2 (A), R8.2
/QSPI_SCLK: U1.52 (QSPI_SCLK), U2.6 (CLK)
/QSPI_SD0: U1.53 (QSPI_SD0), U2.5 (DI/IO_{0})
/QSPI_SD1: U1.55 (QSPI_SD1), U2.2 (DO/IO_{1})
/QSPI_SD2: U1.54 (QSPI_SD2), U2.3 (~WP/IO_{2})
/QSPI_SD3: U1.51 (QSPI_SD3), U2.7 (~HOLD/~RESET/IO_{3})
/QSPI_SS: R10.1, U1.56 (QSPI_SS), U2.1 (~CS)
/ROW0: D1.1 (K), D2.1 (K), D3.1 (K), D4.1 (K), D5.1 (K), D6.1 (K), U1.5 (GPIO3)
/ROW1: D13.1 (K), D14.1 (K), D15.1 (K), D16.1 (K), D17.1 (K), D18.1 (K), U1.6 (GPIO4)
/ROW2: D25.1 (K), D26.1 (K), D27.1 (K), D28.1 (K), D29.1 (K), D30.1 (K), U1.7 (GPIO5)
/ROW3: D37.1 (K), D38.1 (K), D39.1 (K), D40.1 (K), D41.1 (K), D42.1 (K), U1.8 (GPIO6)
/ROW4: D7.1 (K), D8.1 (K), D9.1 (K), D10.1 (K), D11.1 (K), D12.1 (K), U1.38 (GPIO26_ADC0)
/ROW5: D19.1 (K), D20.1 (K), D21.1 (K), D22.1 (K), D23.1 (K), D24.1 (K), U1.37 (GPIO25)
/ROW6: D31.1 (K), D32.1 (K), D33.1 (K), D34.1 (K), D35.1 (K), D36.1 (K), U1.36 (GPIO24)
/ROW7: D43.1 (K), D44.1 (K), D45.1 (K), D46.1 (K), D47.1 (K), D48.1 (K), U1.35 (GPIO23)
/RUN: R9.2, SW1.1, U1.26 (RUN)
/USB_D+: R2.2, U1.47 (USB_DP)
/USB_D-: R3.2, U1.46 (USB_DM)
/VBUS: F1.1, J1.A4 (VBUS), J1.A9 (VBUS), J1.B4 (VBUS), J1.B9 (VBUS), U4.5 (VBUS)
/XIN: C1.1, U1.20 (XIN), Y1.1
/XOUT: R11.1, U1.21 (XOUT)
/XOUT_X: C2.1, R11.2, Y1.2
GND: C1.2, C2.2, C3.2, C6.2, C7.2, C10.2, C11.2, C12.2, C13.2, C14.2, C15.2, C17.2, C18.2, C20.2, C22.2, J1.A1 (GND), J1.A12 (GND), J1.B1 (GND), J1.B12 (GND), J1.S1 (SHIELD), LED1.1 (K), LED2.1 (K), R5.1, R6.1, SW1.2, SW2.2, U1.19 (TESTEN), U1.57 (GND), U2.4 (GND), U3.1 (GND), U4.2 (GND)
unnamed: D1.2 (A), MX1.1
unnamed: D2.2 (A), MX2.1
unnamed: D3.2 (A), MX3.1
unnamed: D4.2 (A), MX4.1
unnamed: D5.2 (A), MX5.1
unnamed: D6.2 (A), MX6.1
unnamed: D7.2 (A), MX7.1
unnamed: D8.2 (A), MX8.1
unnamed: D9.2 (A), MX9.1
unnamed: D10.2 (A), MX10.1
unnamed: D11.2 (A), MX11.1
unnamed: D12.2 (A), MX12.1
unnamed: D13.2 (A), MX13.1
unnamed: D14.2 (A), MX14.1
unnamed: D15.2 (A), MX15.1
unnamed: D16.2 (A), MX16.1
unnamed: D17.2 (A), MX17.1
unnamed: D18.2 (A), MX18.1
unnamed: D19.2 (A), MX19.1
unnamed: D20.2 (A), MX20.1
unnamed: D21.2 (A), MX21.1
unnamed: D22.2 (A), MX22.1
unnamed: D23.2 (A), MX23.1
unnamed: D24.2 (A), MX24.1
unnamed: D25.2 (A), MX25.1
unnamed: D26.2 (A), MX26.1
unnamed: D27.2 (A), MX27.1
unnamed: D28.2 (A), MX28.1
unnamed: D29.2 (A), MX29.1
unnamed: D30.2 (A), MX30.1
unnamed: D31.2 (A), MX31.1
unnamed: D32.2 (A), MX32.1
unnamed: D33.2 (A), MX33.1
unnamed: D34.2 (A), MX34.1
unnamed: D35.2 (A), MX35.1
unnamed: D36.2 (A), MX36.1
unnamed: D37.2 (A), MX37.1
unnamed: D38.2 (A), MX38.1
unnamed: D39.2 (A), MX39.1
unnamed: D40.2 (A), MX40.1
unnamed: D41.2 (A), MX41.1
unnamed: D42.2 (A), MX42.1
unnamed: D43.2 (A), MX43.1
unnamed: D44.2 (A), MX44.1
unnamed: D45.2 (A), MX45.1
unnamed: D46.2 (A), MX46.1
unnamed: D47.2 (A), MX47.1
unnamed: D48.2 (A), MX48.1

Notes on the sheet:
Key matrix (COL2ROW, electrical 8 rows x 6 cols)
MCU (RP2040)
USB-C
Flash / power / USB ESD
Decoupling / clock / reset / boot / LEDs / USB
Mounting holes (M2): H1-H8 case / plate, H9-H12 centre cover
Power flags
eugeo: 6x4x2 ortholinear, RP2040, through-hole on show, Kailh MX hot-swap. Derived from Lumberjack by Paul James (peej), MIT License.

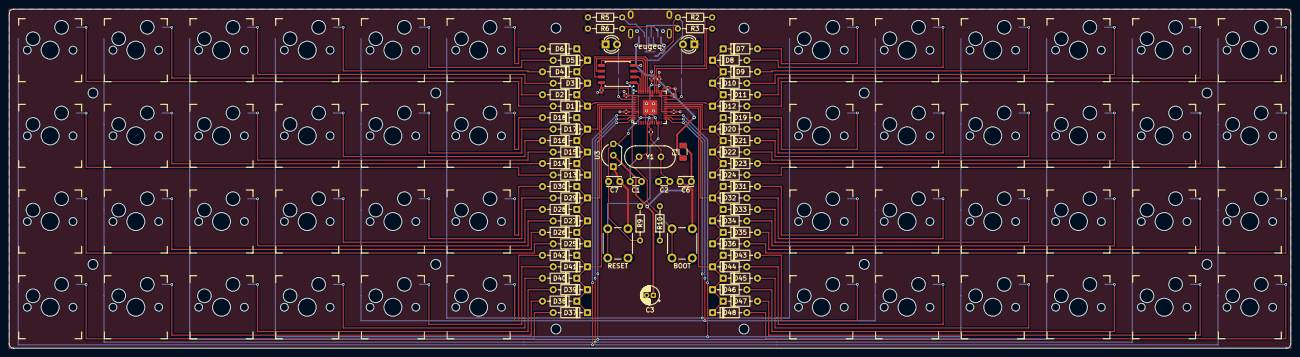
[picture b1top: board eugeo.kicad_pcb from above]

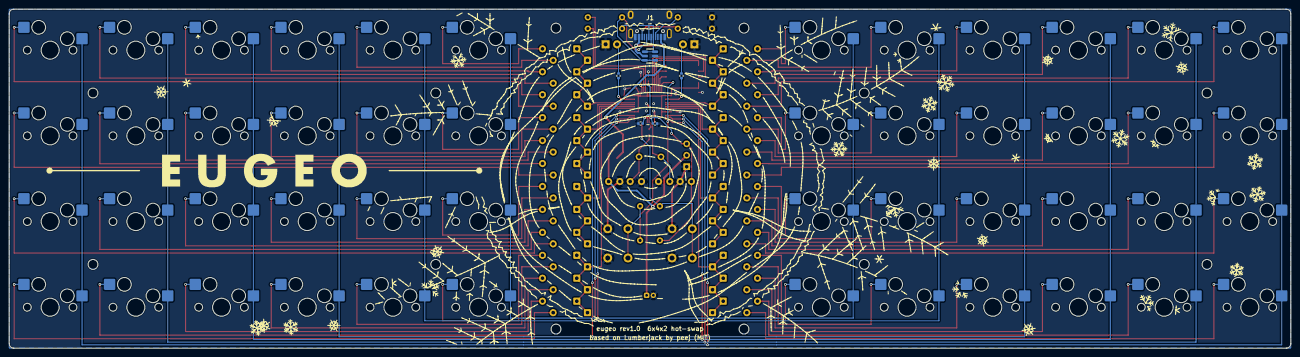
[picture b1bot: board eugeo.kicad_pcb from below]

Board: 2 copper layers, 284.9 x 75.4 mm, 143 parts (6 on the bottom side), 88 nets.

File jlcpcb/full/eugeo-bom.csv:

Comment,Designator,Footprint,LCSC Part #
CPG151101S11 hot-swap socket,"MX1,MX2,MX3,MX4,MX5,MX6,MX7,MX8,MX9,MX10,MX11,MX12,MX13,MX14,MX15,MX16,MX17,MX18,MX19,MX20,MX21,MX22,MX23,MX24,MX25,MX26,MX27,MX28,MX29,MX30,MX31,MX32,MX33,MX34,MX35,MX36,MX37,MX38,MX39,MX40,MX41,MX42,MX43,MX44,MX45,MX46,MX47,MX48",Kailh_MX_Hotswap_Socket,C41430893
22p,"C1,C2",C_Disc_D3.0mm_W1.6mm_P2.50mm,C2170230
100n,"C10,C11,C12,C13,C14,C15,C20,C22",C_0402_1005Metric,C1525
1u,"C17,C18",C_0402_1005Metric,C52923
10u,C3,CP_Radial_D4.0mm_P1.50mm,C43846
1u,"C6,C7",C_Disc_D3.0mm_W2.0mm_P2.50mm,C1620326
1N4148,"D1,D2,D3,D4,D5,D6,D7,D8,D9,D10,D11,D12,D13,D14,D15,D16,D17,D18,D19,D20,D21,D22,D23,D24,D25,D26,D27,D28,D29,D30,D31,D32,D33,D34,D35,D36,D37,D38,D39,D40,D41,D42,D43,D44,D45,D46,D47,D48",D_DO-35_SOD27_P7.62mm_Horizontal,C84410
500mA,F1,Fuse_1206_3216Metric,C75464
USB-C,J1,TYPE-C-31-M-12,C165948
RED,LED1,LED_D3.0mm,C99772
GREEN,LED2,LED_D3.0mm,C85161
1k,R10,R_Axial_DIN0204_L3.6mm_D1.6mm_P7.62mm_Horizontal,C2903331
27R,"R2,R3",R_Axial_DIN0204_L3.6mm_D1.6mm_P7.62mm_Horizontal,C119144
5.1k,"R5,R6",R_Axial_DIN0204_L3.6mm_D1.6mm_P7.62mm_Horizontal,C119195
1k,"R7,R8,R11",R_0402_1005Metric,C11702
10k,R9,R_Axial_DIN0204_L3.6mm_D1.6mm_P7.62mm_Horizontal,C119202
RESET/BOOT,"SW1,SW2",SW_PUSH_6mm,C83205
RP2040,U1,QFN-56-1EP_7x7mm_P0.4mm_EP3.2x3.2mm,C2040
W25Q16JVSSIQ,U2,SOIC-8_5.3x5.3mm_P1.27mm,C131025
MCP1700-3302E,U3,TO-92_Inline_Wide,C511277
USBLC6-2SC6,U4,SOT-23-6,C7519
12MHz,Y1,Crystal_HC49-4H_Vertical,C16369

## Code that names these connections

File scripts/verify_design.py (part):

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    $KP scripts/verify_design.py [lumberjack.net]

Reads the nets straight from eugeo.kicad_pcb and checks the things DRC cannot:
RP2040 pin functions, power / +1V1 / decoupling, crystal, RUN / BOOT, QSPI flash,
USB and LED wiring, diode polarity, and that every key lands where the QMK
keyboard.json says it does.
With a Lumberjack netlist (kicad-cli sch export netlist) it also lists the
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ROOT = os.path.dirname(os.path.dirname(os.path.abspath(__file__)))

# RP2040 QFN-56 pinout, from the RP2040 datasheet (section 1.4.2)
QFN56 = {1: "IOVDD", 2: "GPIO0", 3: "GPIO1", 4: "GPIO2", 5: "GPIO3", 6: "GPIO4", 7: "GPIO5",
         8: "GPIO6", 9: "GPIO7", 10: "IOVDD", 11: "GPIO8", 12: "GPIO9", 13: "GPIO10", 14: "GPIO11",
         15: "GPIO12", 16: "GPIO13", 17: "GPIO14", 18: "GPIO15", 19: "TESTEN", 20: "XIN", 21: "XOUT",
         22: "IOVDD", 23: "DVDD", 24: "SWCLK", 25: "SWD", 26: "RUN", 27: "GPIO16", 28: "GPIO17",
         29: "GPIO18", 30: "GPIO19", 31: "GPIO20", 32: "GPIO21", 33: "IOVDD", 34: "GPIO22",
         35: "GPIO23", 36: "GPIO24", 37: "GPIO25", 38: "GPIO26", 39: "GPIO27", 40: "GPIO28",
         41: "GPIO29", 42: "IOVDD", 43: "ADC_AVDD", 44: "VREG_VIN", 45: "VREG_VOUT", 46: "USB_DM",
         47: "USB_DP", 48: "USB_VDD", 49: "IOVDD", 50: "DVDD", 51: "QSPI_SD3", 52: "QSPI_SCLK",
         53: "QSPI_SD0", 54: "QSPI_SD2", 55: "QSPI_SD1", 56: "QSPI_SS", 57: "GND"}
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
    # --- 3. clock / reset / boot / flash ------------------------------------------
    check(fps["Y1"].GetValue() == "12MHz", "12 MHz crystal (RP2040 boot ROM / USB PLL)")
    check(net("Y1", 1) == fn(20) == "XIN", "Y1 pin 1 on XIN (20)")
    check(two("R11") == {fn(21), net("Y1", 2)} and fps["R11"].GetValue() == "1k", "XOUT (21) -> R11 1k -> Y1 pin 2")
    check(two("C1") == {"XIN", "GND"} and two("C2") == {net("Y1", 2), "GND"}
          and fps["C1"].GetValue() == fps["C2"].GetValue() == "22p", "22 pF load capacitors on both crystal pins")
    check(fn(26) == "RUN" and two("R9") == {"+3V3", "RUN"} and two("SW1") == {"RUN", "GND"},
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        mcu = ({net(r, 1), net(r, 2)} - {a}).pop()
        check(net(led, 1) == "GND" and gpio_of.get(mcu), f"{led}: cathode (pad 1) GND, anode via {r} to {gpio_of.get(mcu)}")
    caps = kb["indicators"]["caps_lock"]
    check(gpio_of[net("R7", 1)] == [caps], f"QMK caps_lock pin {caps} drives LED1")
    src = open(os.path.join(ROOT, "firmware/qmk/keyboards/eugeo/eugeo.c")).read()
    check(f"#define LAYER_LED {gpio_of[net('R8', 1)][0]}" in src, f"eugeo.c layer LED pin is {gpio_of[net('R8', 1)]} (LED2)")
    check(kb["processor"] == "RP2040" and kb["bootloader"] == "rp2040", "QMK processor RP2040 / bootloader rp2040")

    # --- 6. matrix vs QMK ----------------------------------------------------------
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

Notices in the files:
eugeo.kicad_sch:
Derived from Lumberjack (github.com/peej/lumberjack-keyboard) by Paul James, MIT License
